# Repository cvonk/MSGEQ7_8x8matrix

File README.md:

# MSGEQ7 8x8matrix

Spectrum analyzer display using MSGEQ7, 8x8 bicolor matrix and Arduino Uno. Input is from a head phone jack or microphone.

## Demo

Short but powerful.

## Clone

Clone the repository and its submodules to a local directory. The `--recursive` flag automatically initializes and updates the submodules in the repository.

```bash
git clone --recursive https://github.com/cvonk/MSGEQ7_8x8matrix.git
```

or using `ssh`
```bash
git clone --recursive git@github.com:cvonk/MSGEQ7_8x8matrix.git
```

## Hardware

This project uses input from headphone input or amplified microphone and outputs to a 8x8 bicolor matrix.

### Schematic

Power

Logic

A few notes:
- The 200 kΩ resistor is not an E12-series value. You can also make an equivalent value by 220 kΩ and 2.2 MΩ in parallel, or put two 100 kΩ in series.
- If there is noise, try adding a 47 μF across the power rail.
- I put the MSGEQ7 and its glue on a piece of proto board.  

### Bill of materials

Make sure the MSGEQ7 is authentic. It should draw about \(0.8\,\rm{mA}\); pin 6 should have a reference voltage of about \(2.5\,\rm{V}\) and have an indentation near pin 1.

| Name | Description | Suggested mfr and part# | Paid |
|------|-------------|-------------------------|-----:|
| PCB1 | Arduino Uno R3 or compatible | Adafruit 2488 | [$17.50](https://www.adafruit.com/product/2488)
| PCB2 | Bicolor LED Square Pixel Matrix w/ I2C breakout | Adafruit 902 | [$15.95](https://www.adafruit.com/product/902)
| PCB3 | Electret microphone w/ auto gain control | Adafruit 1713 | [$7.95](https://www.adafruit.com/product/1713)
| U1 | Seven Band Graphic Equalizer Display Filter | MSI MSGEQ7 | [$5.50](https://www.digikey.com/en/products/detail/sparkfun-electronics/COM-10468/5806591)
| J1 | Headphone jack stereo connector, 3.5mm, kinked pin | Kycon STX-3120-5B | [$0.74](https://www.digikey.com/en/products/detail/kycon-inc/STX-3120-5B/9990114)
| R1, R2 | Resistor, 22 kOhm, 1%, 1/8 W, 0805 | Yageo RC0805FR-0722KL | [$0.10](https://www.digikey.com/en/products/detail/yageo/RC0805FR-0722KL/727736)
| R3 | Resistor, 200 kOhm, 1%, 1/8 W, 0805 | Yageo RC0805FR-07200KL | [$0.10](https://www.digikey.com/en/products/detail/yageo/RC0805FR-07200KL/7277240)
| C1, C2, C3 | Ceramic capacitor, 0.1 µF, 25V, 0805 | KEMET C0805C104M3RACTU | [$0.10](https://www.digikey.com/en/products/detail/kemet/C0805C104M3RAC7800/2211748)
| C4 | Ceramic capacitor, 33 pF, 50V, 0805 | KEMET C0805C330J5GAC7800 | [$0.10](https://www.digikey.com/en/products/detail/kemet/C0805C330J5GAC7800/411114)

### Notes

The popular Arduino UNO R3 forms the heart of the system. This board is now getting hard to find, but you can also use the Arduino METRO 328 or any other equivalent boards.

For the microphone, I use the Adafruit microphone breakout, because includes an automatic gain control. Other microphones will work for as long as the output signal is strong enough.

## Software

The implementation changes the sound wave to an electrical signal; uses autocorrelation to find frequency played; display frequency as note on screen while sending to a MIDI synthesizer.

### Requirements

| Component | Version tested |
|-----------|----------------|
| Arduino IDE | 1.8.19
| Arduino AVR Boards | 1.8.5
| Adafruit LED Backpack library | 1.3.2
| Adafruit GFX library | 1.11.1

### Build

- Install the libraries.
- Using the Arduino IDE or Visual Code
    - Specify the board and COM port.
    - Build and upload the sketch .

## Details

The [MSI MSGEQ7](http://www.mix-sig.com/images/datasheets/MSGEQ7.pdf) measures the peak voltage in 7 frequency bands. These voltages are multiplexed on one output pin. The timing is shown below, and includes some corrections compared to the datasheet [Maxfield](http://www.eetimes.com/author.asp?doc_id=1323030).

To read each value, we use the `RESET` and `STROBE*` pins.
  - A `RESET` pulse followed by a wait (≥72 μs) resets the multiplexer.
  - On the first falling edge of the strobe signal, the 63 Hz band output propagates to `OUT`. After ≥36 μs, this analog value can be read by the host.
  - Each additional strobe falling edge advances the multiplexer one frequency band (63 &raquo; 160 &raquo; 400 &raquo; 1,000 &raquo; 2,500 &raquo; 6,250 &raquo; 16,000 Hz) and this will repeat indefinitely.

> Each read operation decays the value of that frequency band by approximately 10%. This means that if the Arduino reads less often, e.g. as a result of doing computations, the values read will be higher.

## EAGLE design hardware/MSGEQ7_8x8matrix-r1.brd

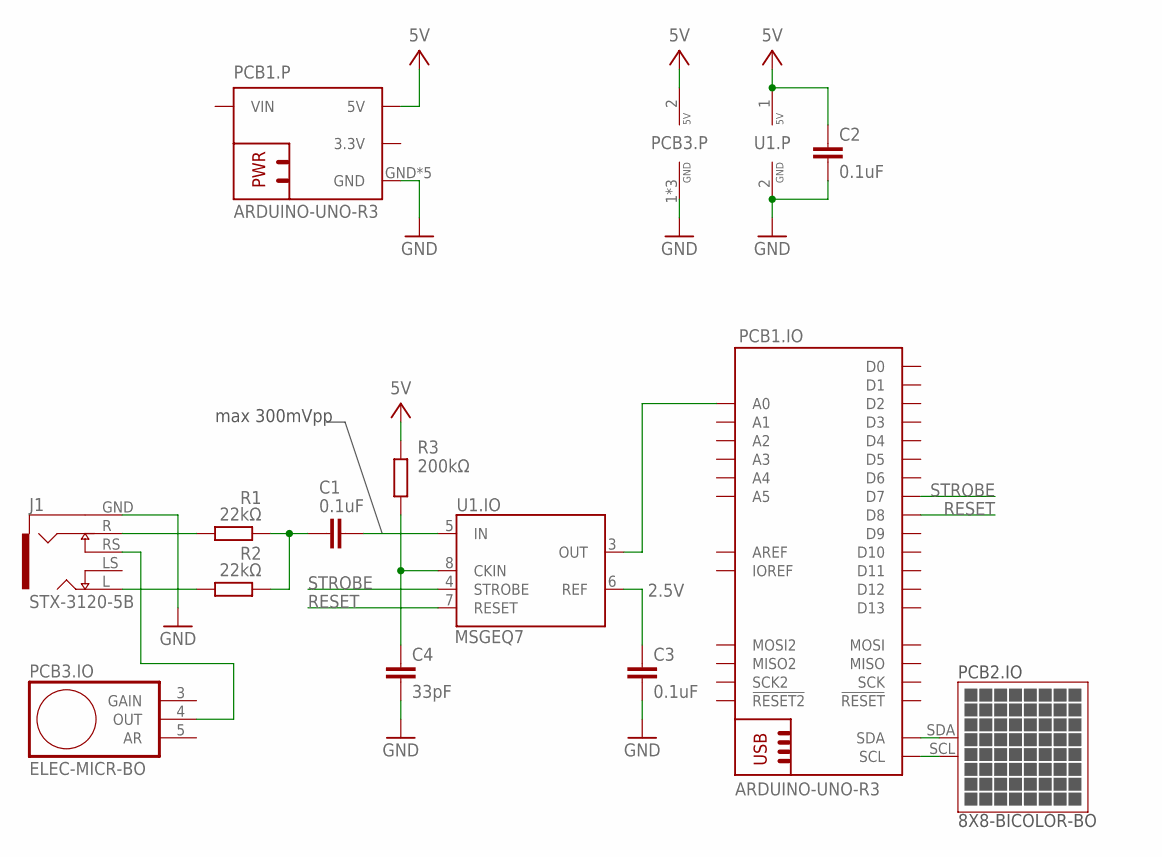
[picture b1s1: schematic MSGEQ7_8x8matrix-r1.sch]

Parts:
C1, C2, C3: 0.1uF; C0805K; MOUSER# 81-GJ821BR61E106KE1L
C4: 33pF; C0805K; MOUSER# 81-GJ821BR61E106KE1L
J1: STX-3120-5B
PCB1: ARDUINO-UNO-R3; ARDUINO-UNO--R3
PCB2: ADAFRUIT-8X8LED-BO; ADAFRUIT-8X8LED
PCB3: ELEC-MICR-BO; ELEC_MICR_BREAKOUT
R1, R2: 22kΩ; R0805; MOUSER# 652-CRM0805JW1R5ELF
R3: 200kΩ; R0805; MOUSER# 652-CRM0805JW1R5ELF
U1: MSGEQ7DIL; DIL-08

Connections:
2.5V: C3.1, U1.6 (REF)
5V: C2.1, PCB1.5V, PCB1.5V@1 (5V), PCB1.5V@2 (5V), PCB3.2 (5V), R3.1, U1.1 (5V)
GND: C2.2, C3.2, C4.2, J1.GND (1), PCB1.GND, PCB1.GND@1 (GND), PCB1.GND@2 (GND), PCB1.GND@3 (GND), PCB1.GND@4 (GND), PCB3.1 (GND), PCB3.P$1 (GND), PCB3.P$2 (GND), U1.2 (GND)
unnamed: J1.R (3), R1.2
unnamed: C1.1, R1.1, R2.1
unnamed: C1.2, U1.5 (IN)
unnamed: J1.L (2), R2.2
unnamed: PCB1.SDA, PCB2.SDA
unnamed: C4.1, R3.2, U1.8 (CKIN)
unnamed: PCB1.A0, U1.3 (OUT)
unnamed: J1.RS (11), PCB3.4 (OUT)
unnamed: PCB1.SCL, PCB2.SCL
RESET: PCB1.D8, U1.7 (RESET)
STROBE: PCB1.D7, U1.4 (STROBE)

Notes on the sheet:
max 300mVpp

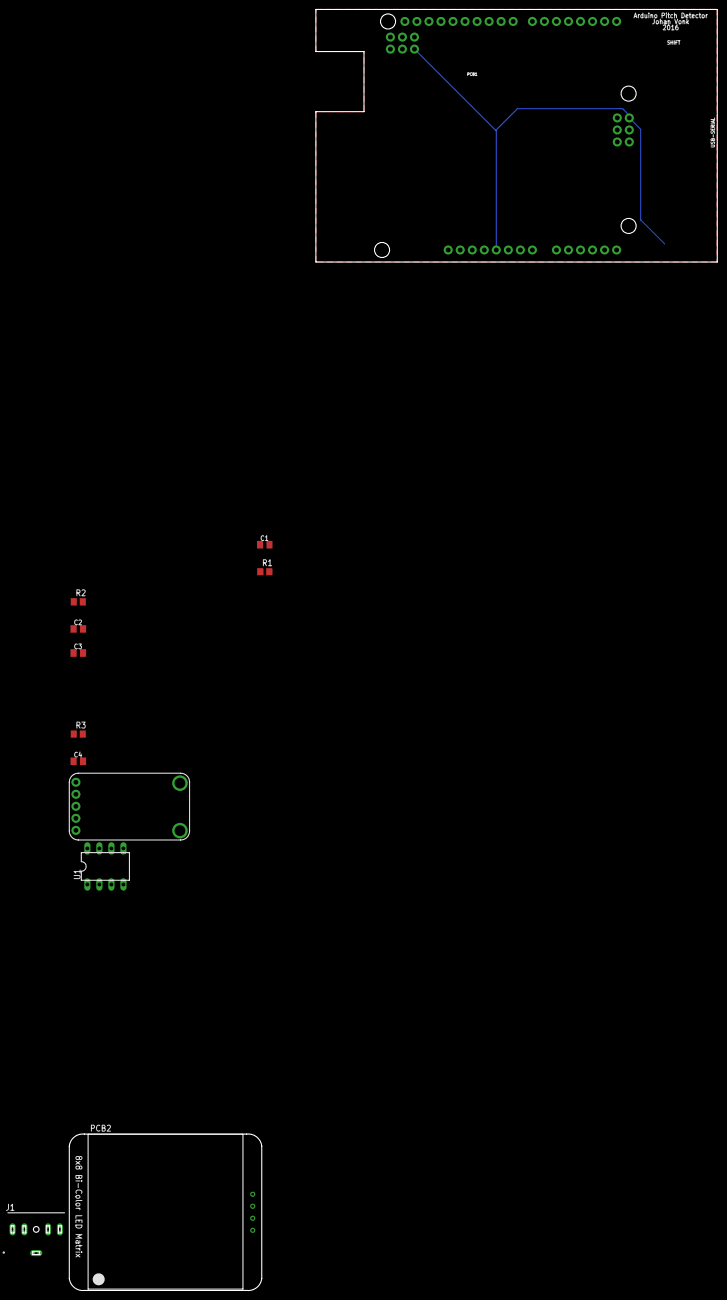
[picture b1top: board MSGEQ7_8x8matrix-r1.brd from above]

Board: 2 copper layers, 149.1 x 270.5 mm, 12 parts (0 on the bottom side), 14 nets.

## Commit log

2022-05-16 initial
2022-05-16 mv to one main.cpp file
2022-05-17 add authentic warning
2022-05-17 add noise warning
